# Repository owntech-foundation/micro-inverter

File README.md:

# An open-source - community built micro-inverter

## Manifesto 

The project goal are : 

- Having the first open source PV micro-inverter
- Finally a design easy to repair that is no longer a black box
- Redeem your data sovereignty, you will no longer depend on a proprietary cloud to follow your solar production and consumption. 

## Open, for everyone, forever

- This project is propulsed by its community. 
- The collective work generated is meant to remain open. 
- Design files are made with open source software - Namely kiCAD.
- Mechanical interfaces and components are modeled using FreeCAD.
- Simulation files use ngSpice.

In that sense, the owntech foundation aims at protecting this technical common.

## Specifications
This section is inspired from [OpenMi](https://github.com/OpenCleanEnergy/OpenMI/)

Comparison of micro-inverters with rated output power between 350VA and 400VA:

| Model                                  | HM-350 | HM-400 | IQ7A |EVT300  |TSOL-M800  |
|:---------------------------------------|:-----------:|:-----------:|:-----------:|:-------------:|:---------------:|
| Manufacturer                           | Hoymiles    | Hoymiles    | Enphase     | Envertech     |    TSUN         |
| Number of solar panels                 | 1           | 1           | 1           | 1             | 2               |
| Recommended input power (W)            | 280-470+    | 320-540+    | 295-460     | 180-420+      |2 $\cdot$ 280-440|
| $V_{MPPT,min}$ (V)                     | 33          | 34          | 38 (18)     | 24            | 33              |
| $V_{MPPT,max}$ (V)                     | 48          | 48          | 43 (58)     | 45            | 48              |
| Start-up voltage (V)                   | 22          | 22          | 22          | -             | -               |
| Operating volage range (V)             | 16-60       | 16-60       | 16-58       | 18-54         | 16-60           |
| Maximum input current (A)              | 11.5        | 12          | 12          | 12            | 11.5            |
| Maximum input short circuit current (A)| 15          | 15          | 20          | 15            | 15              |
| Rated output power (VA)                | 350         | 400         | 349         | 300           | 600             |
| Peak efficiency (%)                    | 96.7        | 96.7        | 97.7        | 95.4          | 96.7            |
| CEC weighted efficiency (%)            | 96.5        | 96.5        | 97.0        | 95.0          | 96.5            |

### uVerter Target specifications

| Category | Requirement | Notes |
|---|---:|---|
| Grid | 220 V AC to 250V AC / 50 to 60 Hz   | Hardware not compatible with 110V grids |
| Grid compliance | Grid-code compliant | Exact certification scope depends on country / standard |
| Rated apparent power | 450 VA | Software-limited power cap supported |
| Input DC operating range | 16 V – 58 V | PV module operating window |
| Recommended PV input power | 350 W – 550 W | Depends on module and thermal conditions |
| Efficiency | > 95% | Target at nominal conditions |
| Power factor | ≈ 1 | Near-unity PF at rated power |
| THD | < 5% | Total harmonic distortion at rated conditions |
| Isolation | Galvanic isolation | Electrical isolation between PV and grid |
| Operating temperature | -40 °C to +60 °C | Derating may apply |
| Repairability | No invasive potting | Designed to be serviceable / inspectable |
| Connectivity | Wi-Fi | Local-first monitoring (no proprietary cloud required) |

## Renderings

## Control overview

The control overview shows the uVerter as two coordinated stages: a PV-controlled DC/DC front end that regulates the panel operating point and raises the DC bus, followed by an AC control stage that shapes a grid-compliant AC output. Measurements and commands flow through Data I/O and the grid-compliance controller so the inverter can synchronize to line/neutral, limit harmonics, and maintain safe operation while power flows from the PV input to the grid.

## Firmware overview

The `firmware/src/main.cpp` file is the entry point for the uVerter firmware: it configures the sensors and power stages, sets up the real-time and background tasks, and runs the state machine plus control loops that drive the boost and inverter legs based on measurements and synchronization status.

- Real-time control runs in `loop_critical_task()` at 100 µs to read sensors, enforce protections, regulate the boost stage, compute duty cycles, and update grid-sync variables.
- Supervisory logic runs in `loop_application_task()` to manage modes (idle/startup/power/error), handle transitions, and expose telemetry through the user data API.

### Compiling

Micro-inverter uses [PlatformIO](https://platformio.org/) as it's build and dependency management system.

#### From the command line

1. Create and activate a Python virtual environment.

        python3 -m venv .owntech-venv
        source .owntech-venv/bin/activate

2. Install PlatformIO.

        pip3 install platformio

3. Compile the code. Dependencies (including Zephyr and Owntech libraries) are downloaded automatically.

        cd micro-inverter/firmware/
        pio run

#### In Visual Studio Code

1. Install the "PlatformIO IDE" extension
2. Open the `firmware` directory via PlatformIO's home screen (**not** with VSCode's File -> Open)
3. Press the "Build" button in the PlatformIO toolbar (found on the bottom left)

## Contribute 

### Spread the word

- ⭐ Star this repository  

- Share the project with PV / power electronics / open-hardware communities  

- Mention it in meetups, forums, maker spaces, or your local energy co-op  

### Give feedback and report issues

Help us improve by opening GitHub issues:

- Bug reports (schematic/PCB mistakes, BOM mismatches, mechanical interferences)  

- Documentation gaps (unclear steps, missing diagrams, confusing naming)  

- Feature requests  

### Choose a contribution path

Start with [Contribute.md](Contribute.md) — a living list of work items the community can pick up.  
Whether you’re a student looking for a thesis topic, an engineer wanting to review a safety-critical design, or a maker growing skills in hardware and firmware: you’re welcome here.  

Bring what you have: time, curiosity, test equipment, careful eyes, lived experience installing or repairing PV gear.  
Let’s build an inverter that isn’t a black box — and keep it open, for everyone, forever.  

## Safety first  

### Disclaimer
This project is shared as-is, without any warranty of any kind, and without any guarantee of compliance with safety, EMC, or grid-connection regulations.
By building, modifying, or using this design, you accept full responsibility for verification, testing, certification (if applicable), and safe operation.

Do not connect a prototype to the public grid.
Grid connection must only happen after appropriate validation, protections, and (where required) third-party certification.

### Mind the risks  
Building a micro-inverter is an advanced DIY project. It combines high energy, high voltage, fast switching, and grid interaction — a mix that can injure, start fires, or damage property

Key hazards include:

- Electric shock and electrocution
Internal stages can reach hundreds of volts. Multiple nets are high voltage. Some capacitors can stay charged after power-off. Treat the system as live until proven discharged and measured.

- Fire and thermal runaway
Faults can turn traces, connectors, inductors, or semiconductors into heaters in seconds. Thermal issues can escalate quickly.

### A community note
We want this project to be open — not reckless. If you spot a safety issue (creepage/clearance, insulation, thermal margins, protection logic, connector ratings, etc.), please report it.
Safety improvements are contributions that protect everyone.

## Standards and directives

### Relevant EU directives for CE

- Directive 2001/95/EC: General Product Safety
- Directive 2014/30/EU: Electromagnetic Compatibility (EMC)
- Directive 2014/35/EU: Low Voltage (LVD)
- Directive 2014/53/EU: Radio Equipment (RED)
- Directive 2011/65/EU: Restriction of the use of certain Hazardous Substances (RoHS)

### Low Voltage Directive (LVD)

**EN IEC 62109-1:2010**
Safety of power converters for use in photovoltaic power systems - Part 1: General requirements

**EN IEC 62109-2:2011**
Safety of power converters for use in photovoltaic power systems - Part 2: Particular requirements for inverters

### Electromagnetic Compatibility (EMC)

**EN 62920:2017+A11+A1:2021**
Photovoltaic power generating systems - EMC requirements and test methods for power conversion equipment

**ETSI EN 301 489-1**
ElectroMagnetic Compatibility (EMC) standard for radio equipment and services; Part 1: Common technical requirements

**ETSI EN 301 489-17**
ElectroMagnetic Compatibility (EMC) standard for radio equipment and services; Part 17: Specific conditions for Broadband Data Transmission Systems

### Radio Equipment Directive (RED)

**ETSI EN 300 328 V2.2.2**
Wideband transmission systems; Data transmission equipment operating in the 2,4 GHz band; Harmonised Standard for access to radio spectrum

### Grid Regulations

As grid regulations are country specific, please refer to [Grid regulations](Grid_regulations.md)

## Licence 

This project is licenced under **CERN-OHL-V2-S** open source hardware licence. Licence file can be found under `License/cern-ohl-v2-s`.

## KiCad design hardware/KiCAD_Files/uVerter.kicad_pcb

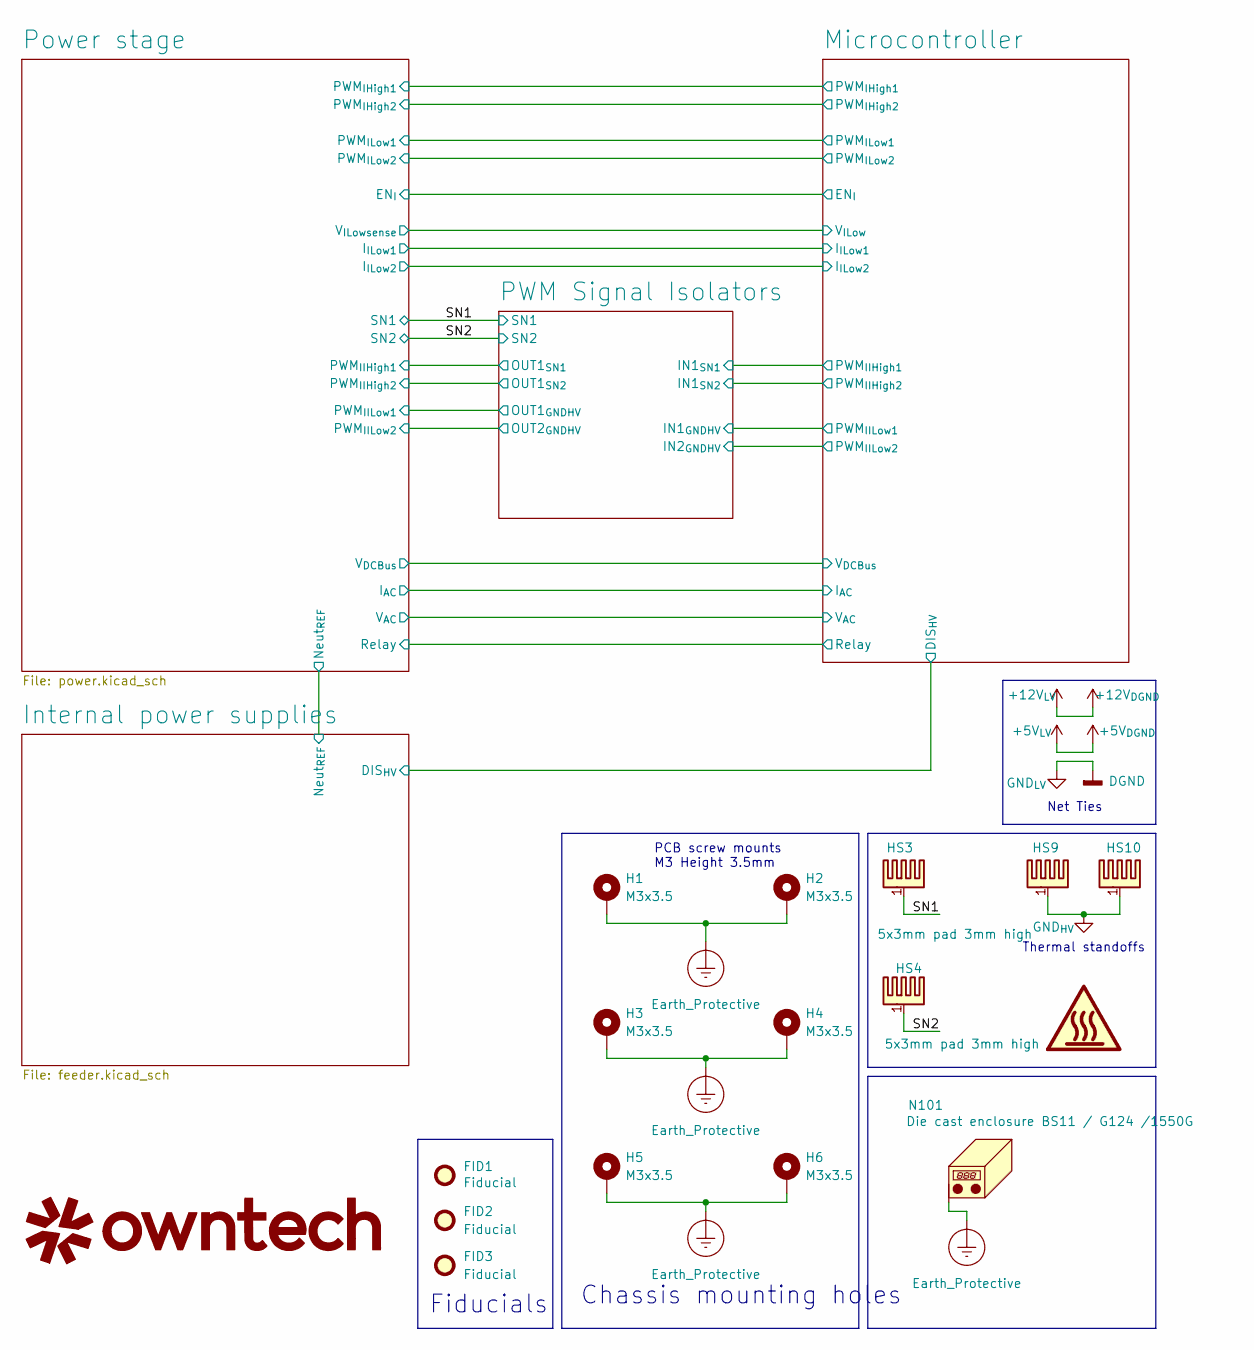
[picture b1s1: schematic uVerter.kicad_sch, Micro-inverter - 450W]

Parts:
FID1, FID2, FID3: Fiducial; Fiducial_1mm_Mask2mm
H1, H2, H3, H4, H5, H6: M3x3.5; MountingHole_Pad_SMD_BD5.6-D4.1; LCSC C2916333
HS3, HS4, HS9, HS10: 5x3mm pad 3mm high; Heatsink_BTC-533-ZN01; LCSC C42404563
Logo1: owntech34mmneg
N101: Die cast enclosure BS11 / G124 /1550G; Die Cast Casing 1550G

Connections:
/SN1: HS3.1; also elsewhere on the board
/SN2: HS4.1; also elsewhere on the board
Earth_Protective: H1.1, H2.1, H3.1, H4.1, H5.1, H6.1, N101.1; also elsewhere on the board
GND_{HV}: HS9.1, HS10.1; also elsewhere on the board

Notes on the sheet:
Thermal standoffs
PCB screw mounts M3 Height 3.5mm
Net Ties
Fiducials
Chassis mounting holes

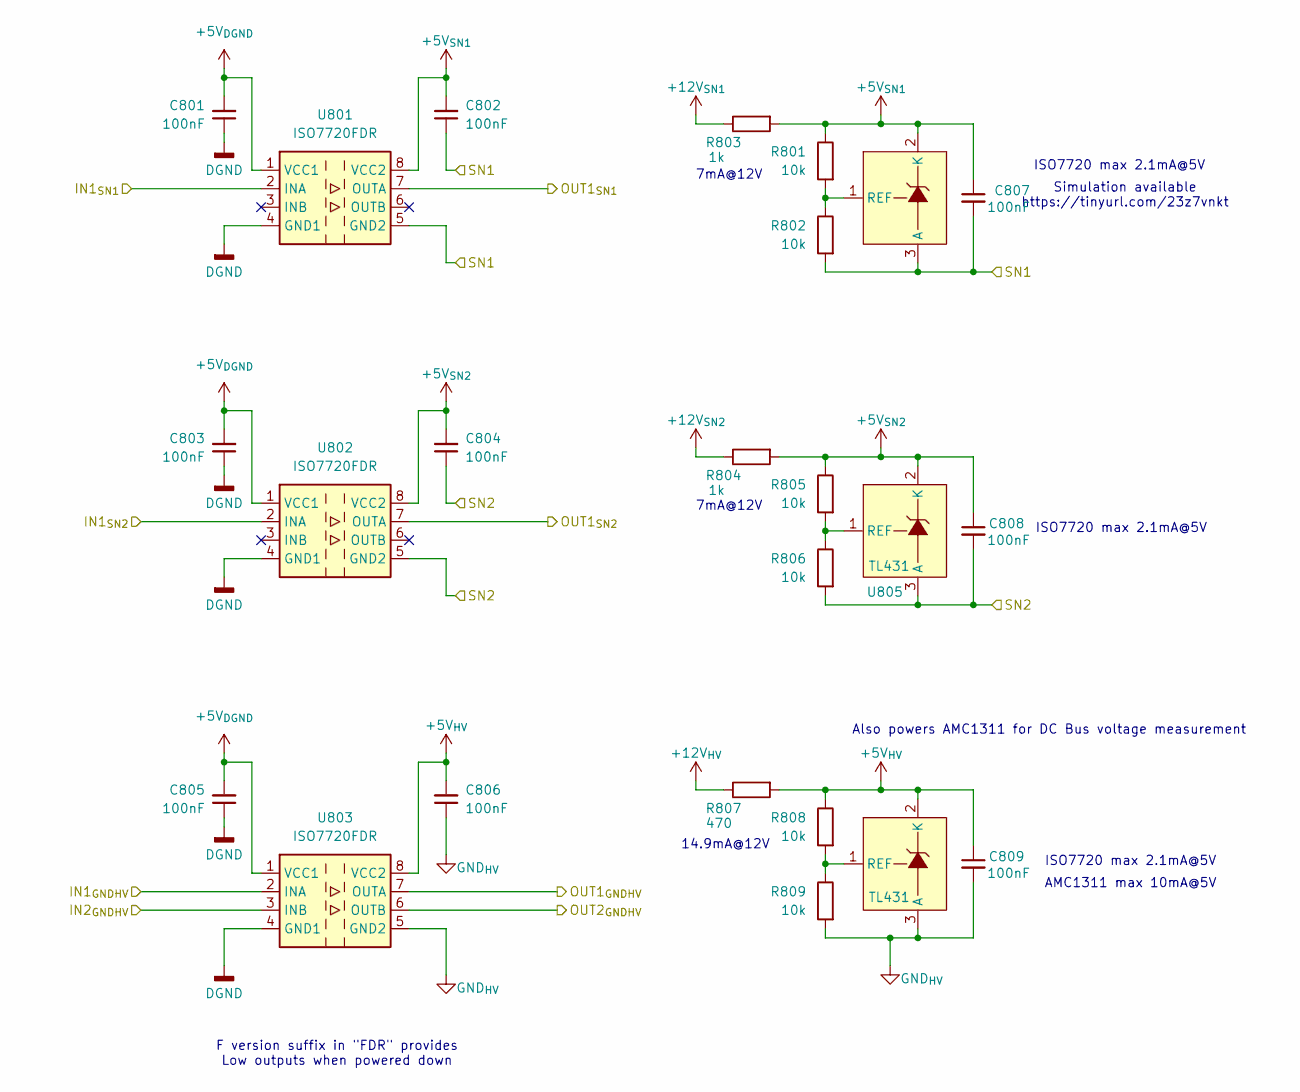
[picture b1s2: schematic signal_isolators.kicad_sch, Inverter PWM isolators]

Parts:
C801, C802, C803, C805, C806: 100nF; C_1206_3216Metric; LCSC C24497
C804, C807, C808, C809: 100nF; C_0805_2012Metric; LCSC C49678
R801, R802, R805, R806, R808, R809: 10k; R_0805_2012Metric; LCSC C17414
R803, R804: 1k; R_0805_2012Metric; LCSC C17513
R807: 470; R_0805_2012Metric; LCSC C17710
U801, U802, U803: ISO7720FDR; SOIC-8_3.9x4.9mm_P1.27mm; LCSC C2878308
U804, U805, U806: TL431; SOT-23; LCSC C181103

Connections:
+5V_{DGND}: C801.2, C803.2, C805.2, U801.1 (VCC1), U802.1 (VCC1), U803.1 (VCC1); also elsewhere on the board
+5V_{HV}: C806.2, C809.1, R807.2, R808.1, U803.8 (VCC2), U806.2 (K); also elsewhere on the board
+5V_{SN1}: C802.2, C807.1, R801.1, R803.2, U801.8 (VCC2), U804.2 (K)
+5V_{SN2}: C804.2, C808.1, R804.2, R805.1, U802.8 (VCC2), U805.2 (K)
+12V_{HV}: R807.1; also elsewhere on the board
+12V_{SN1}: R803.1; also elsewhere on the board
+12V_{SN2}: R804.1; also elsewhere on the board
/Microcontroller/PWM_{IIHigh1}: U801.2 (INA); also elsewhere on the board
/Microcontroller/PWM_{IIHigh2}: U802.2 (INA); also elsewhere on the board
/Microcontroller/PWM_{IILow1}: U803.2 (INA); also elsewhere on the board
/Microcontroller/PWM_{IILow2}: U803.3 (INB); also elsewhere on the board
/PWM Signal Isolators/OUT1_{GNDHV}: U803.7 (OUTA); also elsewhere on the board
/PWM Signal Isolators/OUT1_{SN1}: U801.7 (OUTA); also elsewhere on the board
/PWM Signal Isolators/OUT1_{SN2}: U802.7 (OUTA); also elsewhere on the board
/PWM Signal Isolators/OUT2_{GNDHV}: U803.6 (OUTB); also elsewhere on the board
/SN1: C802.1, C807.2, R802.2, U801.5 (GND2), U804.3 (A); also elsewhere on the board
/SN2: C804.1, C808.2, R806.2, U802.5 (GND2), U805.3 (A); also elsewhere on the board
GND_{HV}: C806.1, C809.2, R809.2, U803.5 (GND2), U806.3 (A); also elsewhere on the board
unnamed: R801.2, R802.1, U804.1 (REF)
unnamed: R805.2, R806.1, U805.1 (REF)
unnamed: R808.2, R809.1, U806.1 (REF)

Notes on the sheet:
ISO7720 max 2.1mA@5V
Also powers AMC1311 for DC Bus voltage measurement
Simulation available https://tinyurl.com/23z7vnkt
AMC1311 max 10mA@5V
7mA@12V
14.9mA@12V
F version suffix in "FDR" provides Low outputs when powered down

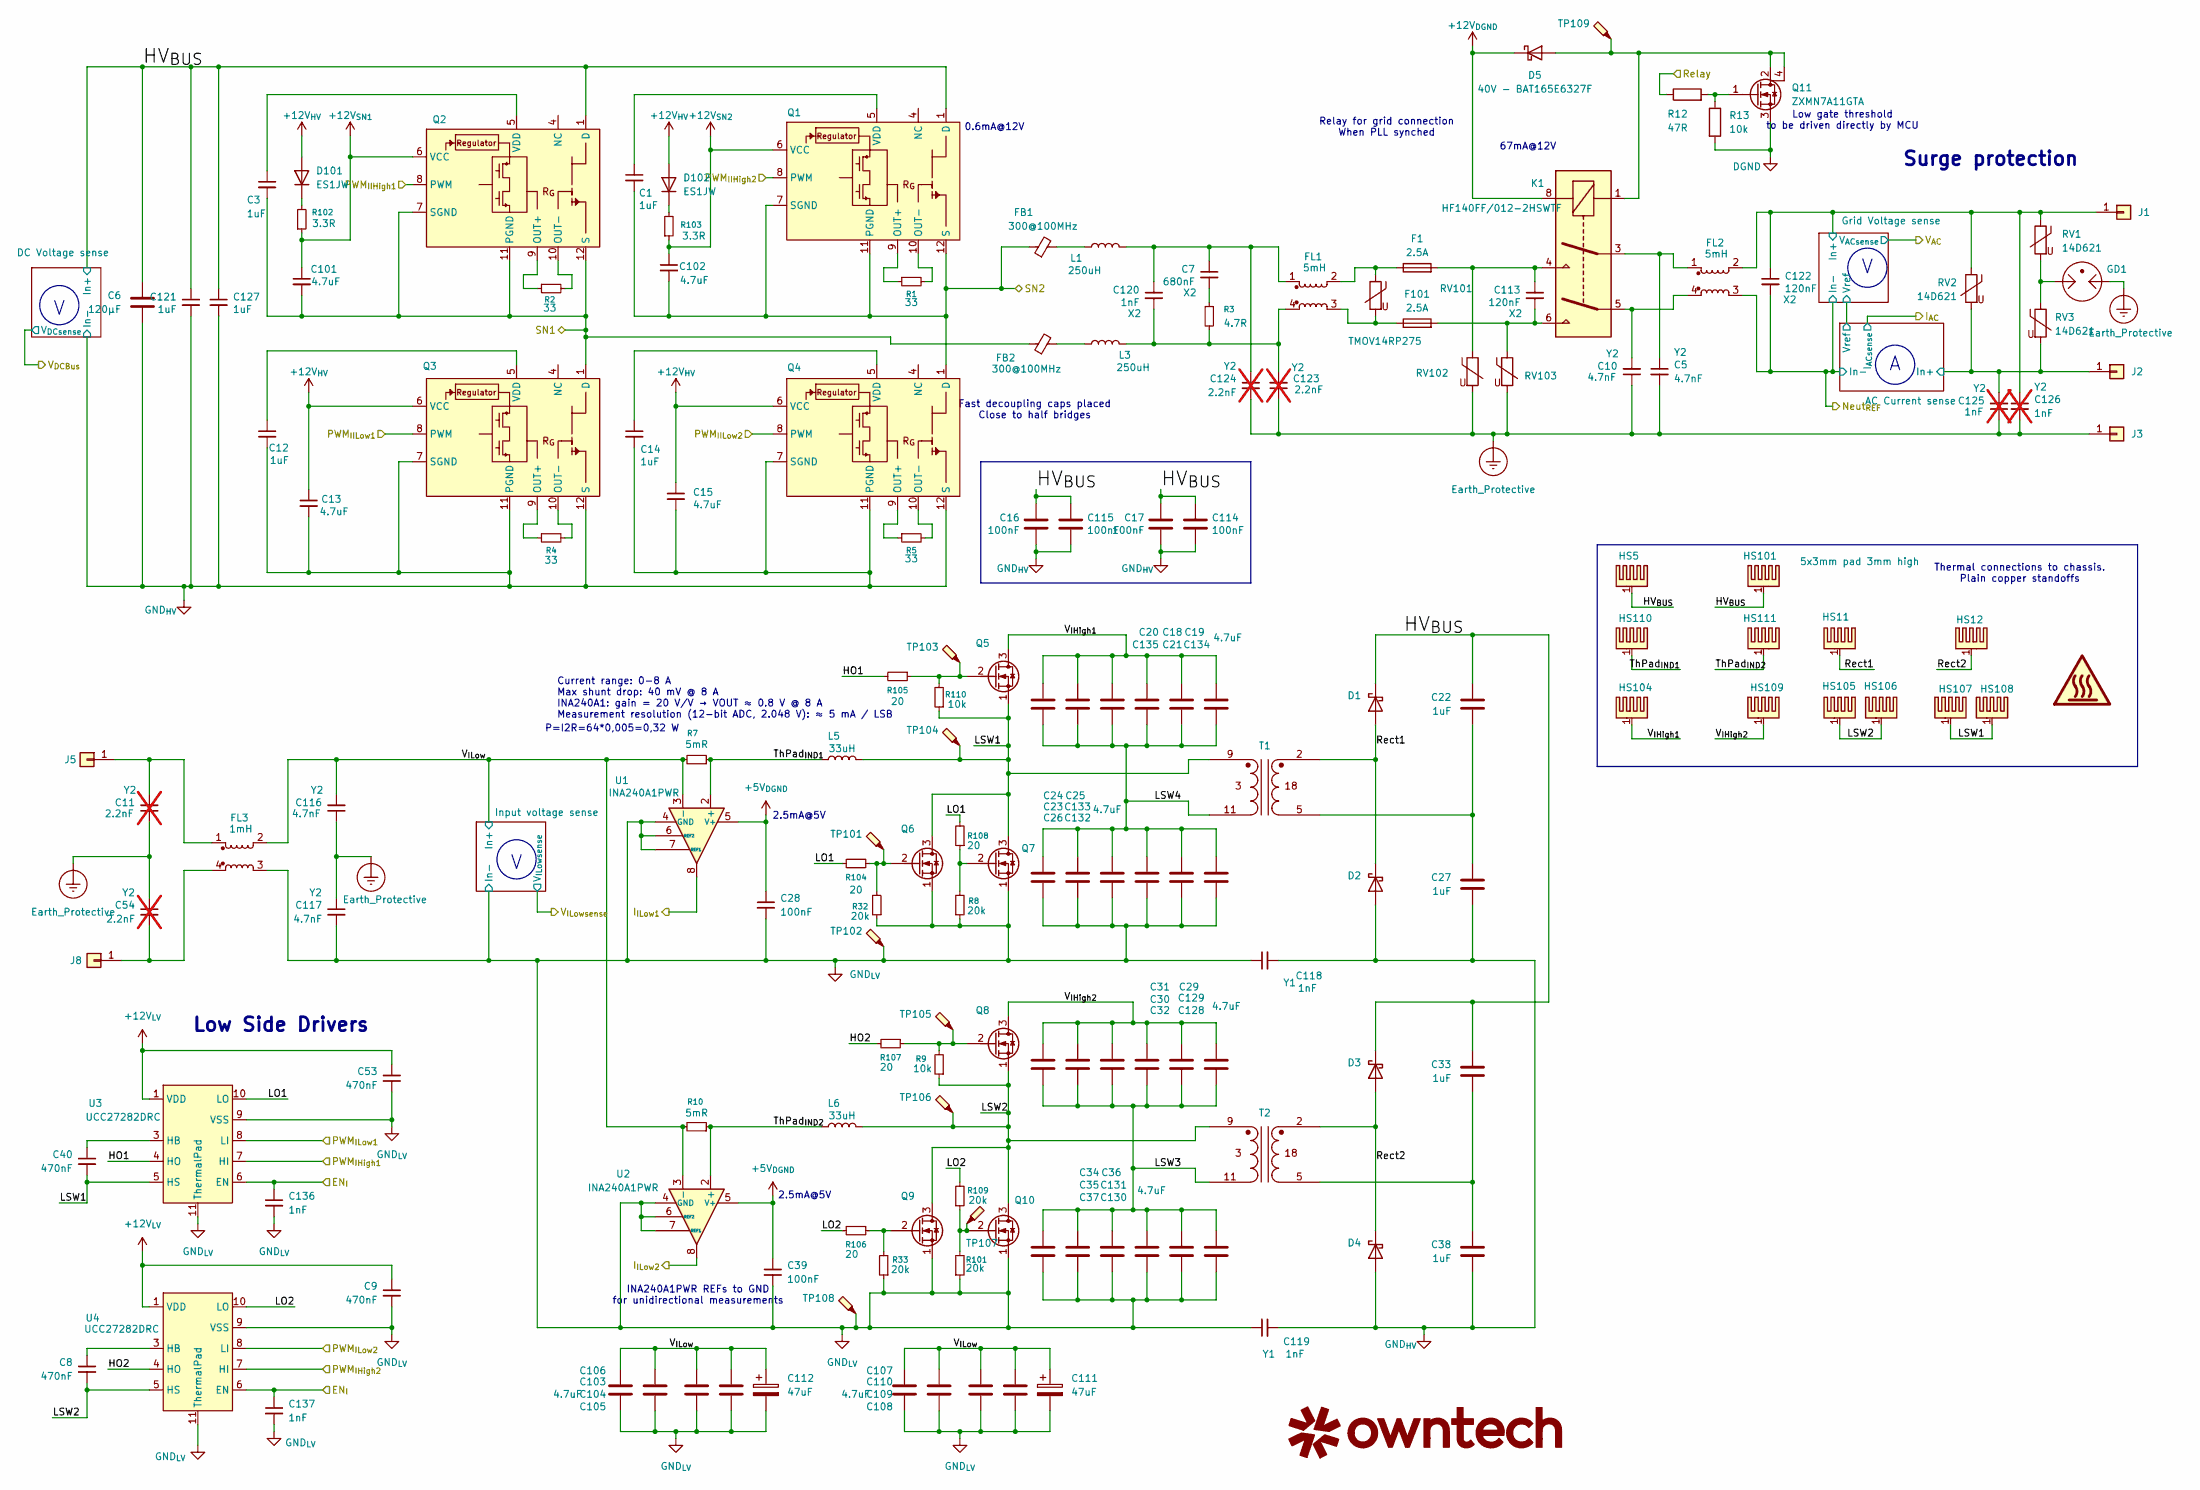
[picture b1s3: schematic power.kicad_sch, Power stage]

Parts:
C1, C3, C12, C14: 1uF; C_0805_2012Metric; LCSC C28323
C5, C10, C116, C117: 4.7nF; C_Rect_L13.0mm_W6.0mm_P10.00mm_FKS3_FKP3_MKS4; LCSC C328768
C6: 120µF; C_film_capacitors_board
C7: 680nF; C_Rect_L18.0mm_W9.0mm_P15.00mm_FKS3_FKP3; LCSC C489081
C8, C9, C40, C53: 470nF; C_0603_1608Metric; LCSC C1623
C11, C54: 2.2nF; C_Rect_L9.0mm_W4.0mm_P7.50mm_MKT; LCSC C5121878; not fitted
C13, C15, C101, C102: 4.7uF; C_0805_2012Metric; LCSC C1779
C16, C17, C114, C115: 100nF; C_1210_3225Metric; Voltage_Rating 600V; LCSC C22374890
C18, C19, C20, C21, C23, C24, C25, C26, C29, C30, C31, C32, C34, C35, C36, C37, C103, C104, C105, C106, C107, C108, C109, C110, C128, C129, C130, C131, C132, C133, C134, C135: 4.7uF; C_1210_3225Metric; LCSC C381466
C22, C27, C33, C38, C121, C127: 1uF; C_Rect_L18.0mm_W8.0mm_P15.00mm_FKS3_FKP3; LCSC C7529557
C28, C39: 100nF; C_0805_2012Metric; LCSC C49678
C111, C112: 47uF; C_Elec_10x10.2; LCSC C3031594
C113, C122: 120nF; C_Rect_L13.0mm_W6.0mm_P10.00mm_FKS3_FKP3_MKS4; LCSC C46638860
C118, C119: 1nF; C_TH_L6.3-W4.4-P10.00-D0.6-S3.8; LCSC C2974845
C120: 1nF; C_Rect_L10.3mm_W4.5mm_P7.50mm_MKS4; LCSC C47278939
C123, C124: 2.2nF; C_Rect_L10.3mm_W4.5mm_P7.50mm_MKS4; LCSC C5121878; not fitted
C125, C126: 1nF; C_Rect_L10.3mm_W4.5mm_P7.50mm_MKS4; LCSC C5121878; not fitted
C136, C137: 1nF; C_0603_1608Metric; LCSC C1588
D1, D2, D3, D4: D_Schottky; TO-252-2_Diode; LCSC C967703
D5: 40V - BAT165E6327F; D_SOD-323; LCSC C42411276
D101, D102: ES1JW; D_SOD-123; LCSC C108815
F1, F101: 2.5A; FUSE-TH_L8.4-W4.1-P5.08-D0.6; LCSC C2995772
FB1, FB2: 300@100MHz; L_1206_3216Metric; LCSC C703115
FL1, FL2: 5mH; Choke_TH_XRSQ1515-5MH-V-1013; LCSC C30584795
FL3: 1mH; Choke_TH_4P-L23.0-W15.0-P7.50-D1.0-S9.0; LCSC C2997440
GD1: 2R600B-8S; SMD_GDT; LCSC C42246321
HS5, HS11, HS12, HS101, HS104, HS105, HS106, HS107, HS108, HS109, HS110, HS111: 5x3mm pad 3mm high; Heatsink_BTC-533-ZN01; LCSC C42404563
J1, J2, J3, J5, J8: Conn_01x01; Connector_SMD-4_TS34056055-0440; LCSC C19724594
K1: HF140FF/012-2HSWTF; RELAY-TH_HF140FF-024-2HSWT; LCSC C5322766
L1, L3: 250uH; L_SMD_L28.0-W23-LS25; LCSC C42422423
L5, L6: 33uH; L_SRP1510CA-330M; LCSC C18236320
Logo101: owntech21mm
Q1, Q2, Q3, Q4: CID12N65D; DFN-10_L8.0-W6.0_CID12N65D; LCSC C21547657
Q5, Q6, Q7, Q8, Q9, Q10: CJAC90SN12; DFN-8-1EP_5x6_P1.27mm; LCSC C504097
Q11: ZXMN7A11GTA; SOT-223; LCSC C460277
R1, R2, R4, R5: 33; R_0805_2012Metric; LCSC C17634
R3: 4.7R; R_2512_6332Metric; LCSC C2897629
R7, R10: 5mR; R_2512_6332Metric; LCSC C393074
R8, R32, R33, R101, R109: 20k; R_0603_1608Metric; LCSC C4184
R9, R110: 10k; R_0603_1608Metric; LCSC C25804
R12: 47R; R_0805_2012Metric; LCSC C17714
R13: 10k; R_0805_2012Metric; LCSC C17414
R102, R103: 3.3R; R_0805_2012Metric; LCSC C16257
R104, R105, R106, R107, R108: 20; R_0603_1608Metric; LCSC C22950
RV1, RV2, RV3: 14D621; RV_Disc_D15.5mm_W11mm_P7.5mm; LCSC C774640
RV101, RV102, RV103: TMOV14RP275; RV_Disc_D12mm_W6.2mm_P7.5mm; LCSC C1528070
T1, T2: Transformer_1P_1S; RM12
TP101, TP103, TP105, TP107: TestPoint_Probe; TestPoint_Pad_D0.5mm
TP102, TP104, TP106, TP108, TP109: TestPoint_Probe; TestPoint_Pad_D1.0mm
U1, U2: INA240A1PWR; TSSOP-8_4.4x3mm_P0.65mm; LCSC C93965
U3, U4: UCC27282DRC; VSON-10_L3.0-W3.0-P0.50-TL-EP; LCSC C2677035

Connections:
+5V_{DGND}: C28.1, C39.1, U1.5 (V+), U2.5 (V+); also elsewhere on the board
+12V_{HV}: C13.1, C15.1, D101.2 (A), D102.2 (A), Q3.6 (VCC), Q4.6 (VCC); also elsewhere on the board
+12V_{SN1}: C101.1, Q2.6 (VCC), R102.1; also elsewhere on the board
+12V_{SN2}: C102.1, Q1.6 (VCC), R103.1; also elsewhere on the board
/Internal power supplies/Neut_{REF}: C122.2, FL2.3; also elsewhere on the board
/Microcontroller/EN_{I}: C136.1, C137.1, U3.6 (EN), U4.6 (EN); also elsewhere on the board
/Microcontroller/I_{ILow1}: U1.8; also elsewhere on the board
/Microcontroller/I_{ILow2}: U2.8; also elsewhere on the board
/Microcontroller/PWM_{IHigh1}: U3.7 (HI); also elsewhere on the board
/Microcontroller/PWM_{IHigh2}: U4.7 (HI); also elsewhere on the board
/Microcontroller/PWM_{ILow1}: U3.8 (LI); also elsewhere on the board
/Microcontroller/PWM_{ILow2}: U4.8 (LI); also elsewhere on the board
/Microcontroller/Relay: R12.1; also elsewhere on the board
/PWM Signal Isolators/OUT1_{GNDHV}: Q3.8 (PWM); also elsewhere on the board
/PWM Signal Isolators/OUT1_{SN1}: Q2.8 (PWM); also elsewhere on the board
/PWM Signal Isolators/OUT1_{SN2}: Q1.8 (PWM); also elsewhere on the board
/PWM Signal Isolators/OUT2_{GNDHV}: Q4.8 (PWM); also elsewhere on the board
/Power stage/AC Current sense/In+: C125.2, J2.1, RV2.2, RV3.2; also elsewhere on the board
/Power stage/Grid Voltage sense/In+: C122.1, C126.1, FL2.2, J1.1, RV1.1, RV2.1; also elsewhere on the board
/Power stage/HO1: R105.2, U3.4 (HO)
/Power stage/HO2: R107.2, U4.4 (HO)
/Power stage/HV_{BUS}: C6.1, C16.1, C17.1, C22.1, C33.1, C114.1, C115.1, C121.1, C127.1, D1.1 (K), D3.1 (K), HS5.1, HS101.1, Q1.1 (D), Q2.1 (D); also elsewhere on the board
/Power stage/LO1: R104.2, R108.2, U3.10 (LO)
/Power stage/LO2: R106.2, R109.2, U4.10 (LO)
/Power stage/LSW1: C40.2, HS107.1, HS108.1, L5.2, Q5.1 (S), Q6.3 (D), Q7.3 (D), R110.1, T1.8 (AA), T1.9 (AA), TP104.1, U3.5 (HS)
/Power stage/LSW2: C8.2, HS105.1, HS106.1, L6.2, Q8.1 (S), Q9.3 (D), Q10.3 (D), R9.1, T2.8 (AA), T2.9 (AA), TP106.1, U4.5 (HS)
/Power stage/LSW3: C29.2, C30.2, C31.2, C32.2, C34.1, C35.1, C36.1, C37.1, C128.2, C129.2, C130.1, C131.1, T2.11 (AB), T2.12 (AB)
/Power stage/LSW4: C18.2, C19.2, C20.2, C21.2, C23.1, C24.1, C25.1, C26.1, C132.1, C133.1, C134.2, C135.2, T1.11 (AB), T1.12 (AB)
/Power stage/Rect1: D1.2 (A), D2.1 (K), HS11.1, T1.2 (SB)
/Power stage/Rect2: D3.2 (A), D4.1 (K), HS12.1, T2.2 (SB)
/Power stage/ThPad_{IND1}: HS110.1, L5.1, R7.1, U1.2 (+)
/Power stage/ThPad_{IND2}: HS111.1, L6.1, R10.1, U2.2 (+)
/Power stage/V_{IHigh1}: C18.1, C19.1, C20.1, C21.1, C134.1, C135.1, HS104.1, Q5.3 (D)
/Power stage/V_{IHigh2}: C29.1, C30.1, C31.1, C32.1, C128.1, C129.1, HS109.1, Q8.3 (D)
/Power stage/V_{ILow}: C103.2, C104.2, C105.2, C106.2, C107.2, C108.2, C109.2, C110.2, C111.1, C112.1, C116.2, FL3.2, R7.2, R10.2, U1.3 (-), U2.3 (-); also elsewhere on the board
/SN1: C3.2, C101.2, FB2.1, Q2.7 (SGND), Q2.11 (PGND), Q2.12 (S), Q3.1 (D); also elsewhere on the board
/SN2: C1.2, C102.2, FB1.1, Q1.7 (SGND), Q1.11 (PGND), Q1.12 (S), Q4.1 (D); also elsewhere on the board
Earth_Protective: C5.2, C10.1, C11.1, C54.1, C116.1, C117.1, C123.1, C124.2, C125.1, C126.2, GD1.1, J3.1, RV102.2, RV103.2; also elsewhere on the board
GND_{HV}: C6.2, C12.2, C13.2, C14.2, C15.2, C16.2, C17.2, C27.2, C38.2, C114.2, C115.2, C118.2, C119.2, C121.2, C127.2, D2.2 (A), D4.2 (A), Q3.7 (SGND), Q3.11 (PGND), Q3.12 (S), Q4.7 (SGND), Q4.11 (PGND), Q4.12 (S); also elsewhere on the board
unnamed: C5.1, FL2.1, K1.3
unnamed: C7.2, R3.1
unnamed: C10.2, FL2.4, K1.5
unnamed: C113.1, F1.2, K1.4, RV102.1
unnamed: C113.2, F101.2, K1.6, RV103.1
unnamed: C7.1, C120.1, C124.1, FL1.1, L1.2
unnamed: C120.2, C123.2, FL1.4, L3.2, R3.2
unnamed: D5.2 (A), K1.1, Q11.2 (D), Q11.4 (D), TP109.1
unnamed: D101.1 (K), R102.2
unnamed: D102.1 (K), R103.2
unnamed: F1.1, FL1.2, RV101.1
unnamed: F101.1, FL1.3, RV101.2
unnamed: FB1.2, L1.1
unnamed: FB2.2, L3.1
unnamed: GD1.3, RV1.2, RV3.1
unnamed: C11.2, FL3.1, J5.1
unnamed: C54.2, FL3.4, J8.1
unnamed: Q1.9 (OUT+), R1.1
unnamed: Q1.10 (OUT-), R1.2
unnamed: C1.1, Q1.5 (VDD)
unnamed: Q2.9 (OUT+), R2.1
unnamed: Q2.10 (OUT-), R2.2
unnamed: C3.1, Q2.5 (VDD)
unnamed: Q3.9 (OUT+), R4.1
unnamed: Q3.10 (OUT-), R4.2
unnamed: C12.1, Q3.5 (VDD)
unnamed: Q4.9 (OUT+), R5.1
unnamed: Q4.10 (OUT-), R5.2
unnamed: C14.1, Q4.5 (VDD)
unnamed: Q5.2 (G), R105.1, R110.2, TP103.1
unnamed: Q6.2 (G), R32.2, R104.1, TP101.1
unnamed: Q7.2 (G), R8.2, R108.1
unnamed: Q8.2 (G), R9.2, R107.1, TP105.1
unnamed: Q9.2 (G), R33.2, R106.1
unnamed: Q10.2 (G), R101.2, R109.1, TP107.1
unnamed: Q11.1 (G), R12.2, R13.1
unnamed: C22.2, C27.1, T1.5 (SA)
unnamed: C33.2, C38.1, T2.5 (SA)
unnamed: C40.1, U3.3 (HB)
unnamed: C8.1, U4.3 (HB)

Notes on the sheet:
Surge protection
P=I2R=64*0,005=0,32 W
Low gate threshold to be driven directly by MCU
2.5mA@5V
Thermal connections to chassis. Plain copper standoffs
Current range: 0-8 A Max shunt drop: 40 mV @ 8 A INA240A1: gain = 20 V/V → VOUT ≈ 0.8 V @ 8 A Measurement resolution (12-bit ADC, 2.048 V): ≈ 5 mA / LSB
Low Side Drivers
67mA@12V
Fast decoupling caps placed Close to half bridges
INA240A1PWR REFs to GND for unidirectional measurements
Relay for grid connection When PLL synched
0.6mA@12V

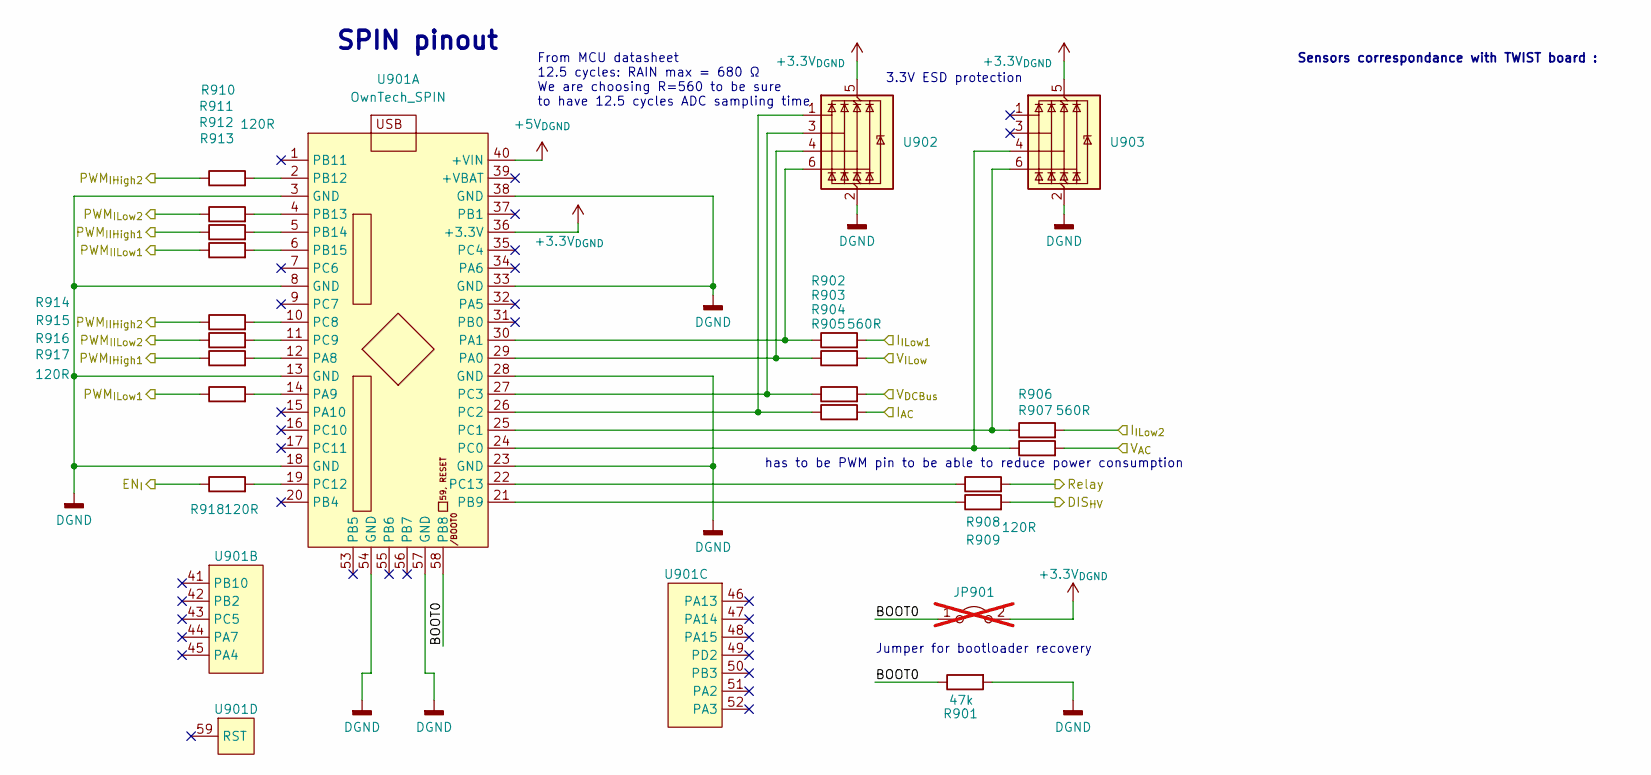
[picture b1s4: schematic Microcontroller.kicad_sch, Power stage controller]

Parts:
JP901: Jumper_2_Open; PinHeader_1x02_P2.54mm_Vertical; not fitted
R901: 47k; R_0805_2012Metric; LCSC C17713
R902, R903, R904, R905, R906, R907: 560R; R_0805_2012Metric; LCSC C28636
R908, R909, R910, R911, R912, R913, R914, R915, R916, R917, R918: 120R; R_0805_2012Metric; LCSC C17437
U901: OwnTech_SPIN; OwnTech_SPINTHT_1
U902, U903: WE-TVS-824015043; SOT-363_SC-70-6; LCSC C1869321

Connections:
+3.3V_{DGND}: JP901.2 (B), U901.36 (+3.3V), U902.5 (VBUS), U903.5 (VBUS)
+5V_{DGND}: U901.40 (+VIN); also elsewhere on the board
/Internal power supplies/DIS_{HV}: R909.2; also elsewhere on the board
/Microcontroller/BOOT0: JP901.1 (A), R901.1, U901.58 (PB8)
/Microcontroller/EN_{I}: R918.1; also elsewhere on the board
/Microcontroller/I_{AC}: R905.2; also elsewhere on the board
/Microcontroller/I_{ILow1}: R902.2; also elsewhere on the board
/Microcontroller/I_{ILow2}: R906.2; also elsewhere on the board
/Microcontroller/PWM_{IHigh1}: R916.1; also elsewhere on the board
/Microcontroller/PWM_{IHigh2}: R910.1; also elsewhere on the board
/Microcontroller/PWM_{IIHigh1}: R912.1; also elsewhere on the board
/Microcontroller/PWM_{IIHigh2}: R914.1; also elsewhere on the board
/Microcontroller/PWM_{IILow1}: R913.1; also elsewhere on the board
/Microcontroller/PWM_{IILow2}: R915.1; also elsewhere on the board
/Microcontroller/PWM_{ILow1}: R917.1; also elsewhere on the board
/Microcontroller/PWM_{ILow2}: R911.1; also elsewhere on the board
/Microcontroller/Relay: R908.2; also elsewhere on the board
/Microcontroller/V_{AC}: R907.2; also elsewhere on the board
/Microcontroller/V_{DCBus}: R904.2; also elsewhere on the board
/Microcontroller/V_{ILow}: R903.2; also elsewhere on the board
unnamed: R903.1, U901.29 (PA0), U902.4 (I/O3)
unnamed: R902.1, U901.30 (PA1), U902.6 (I/O4)
unnamed: R916.2, U901.12 (PA8)
unnamed: R917.2, U901.14 (PA9)
unnamed: R909.1, U901.21 (PB9)
unnamed: R910.2, U901.2 (PB12)
unnamed: R911.2, U901.4 (PB13)
unnamed: R912.2, U901.5 (PB14)
unnamed: R913.2, U901.6 (PB15)
unnamed: R907.1, U901.24 (PC0), U903.4 (I/O3)
unnamed: R906.1, U901.25 (PC1), U903.6 (I/O4)
unnamed: R905.1, U901.26 (PC2), U902.1 (I/O1)
unnamed: R904.1, U901.27 (PC3), U902.3 (I/O2)
unnamed: R914.2, U901.10 (PC8)
unnamed: R915.2, U901.11 (PC9)
unnamed: R918.2, U901.19 (PC12)
unnamed: R908.1, U901.22 (PC13)

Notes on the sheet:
Jumper for bootloader recovery
From MCU datasheet 12.5 cycles: RAIN max = 680 Ω We are choosing R=560 to be sure to have 12.5 cycles ADC sampling time
has to be PWM pin to be able to reduce power consumption
Sensors correspondance with TWIST board :
SPIN pinout
3.3V ESD protection

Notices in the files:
Microcontroller.kicad_sch:
CopyLeft LibreSolar
